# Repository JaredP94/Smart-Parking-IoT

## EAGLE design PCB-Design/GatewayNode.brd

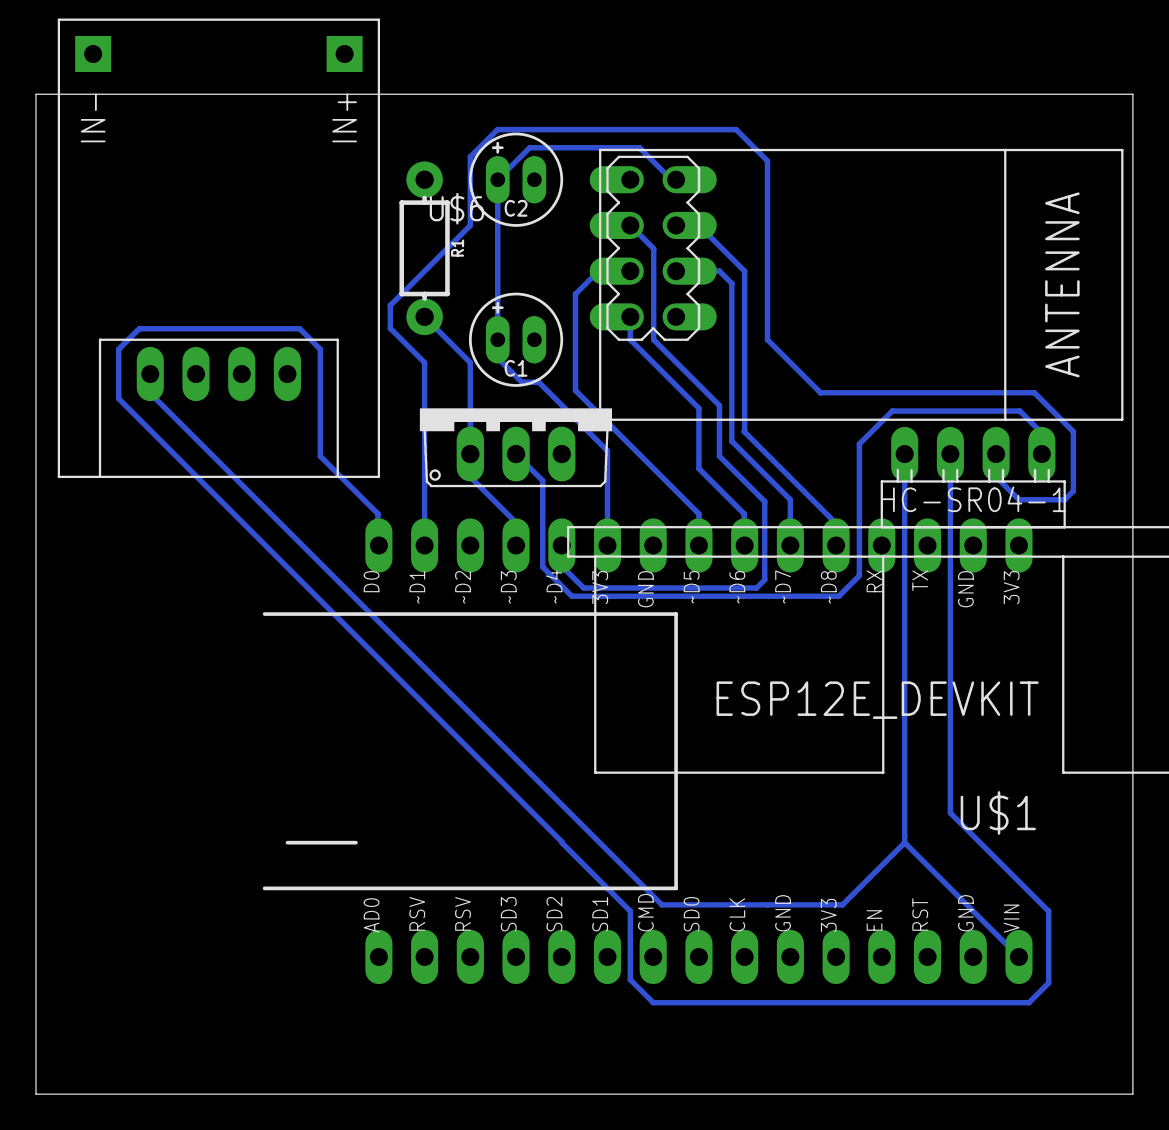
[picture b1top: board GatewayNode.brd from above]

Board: 2 copper layers, 60.9 x 55.5 mm, 8 parts (0 on the bottom side), 12 nets.

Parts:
C1, C2: 10U/35V; E2-5
HC-SR04-1: ULTRASONIC-HC-SR04#V
M3: WIRELESS-NRF24L01
R1: 10k; AXIAL-0.3-KIT
U$1: ESP12E_DEVKIT
U$5: DC-DC-STEP-UP-5V
U$6: IRL520N; TO220-VERT

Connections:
GND: C1.-, C2.-, M3.1, R1.P$1, U$1.GND@0, U$1.GND@1, U$1.GND@2, U$1.GND@3, U$5.GND, U$6.3
unnamed: R1.P$2, U$1.D3, U$6.1
unnamed: C1.+, C2.+, M3.2, U$1.3V3@1
unnamed: M3.3, U$1.D4
unnamed: M3.5, U$1.D5
unnamed: M3.7, U$1.D6
unnamed: M3.4, U$1.D8
unnamed: M3.6, U$1.D7
unnamed: HC-SR04-1.2, U$1.D0
unnamed: HC-SR04-1.4, U$6.2
unnamed: HC-SR04-1.3, U$1.D1
VCC: HC-SR04-1.1, U$1.VIN, U$5.5V

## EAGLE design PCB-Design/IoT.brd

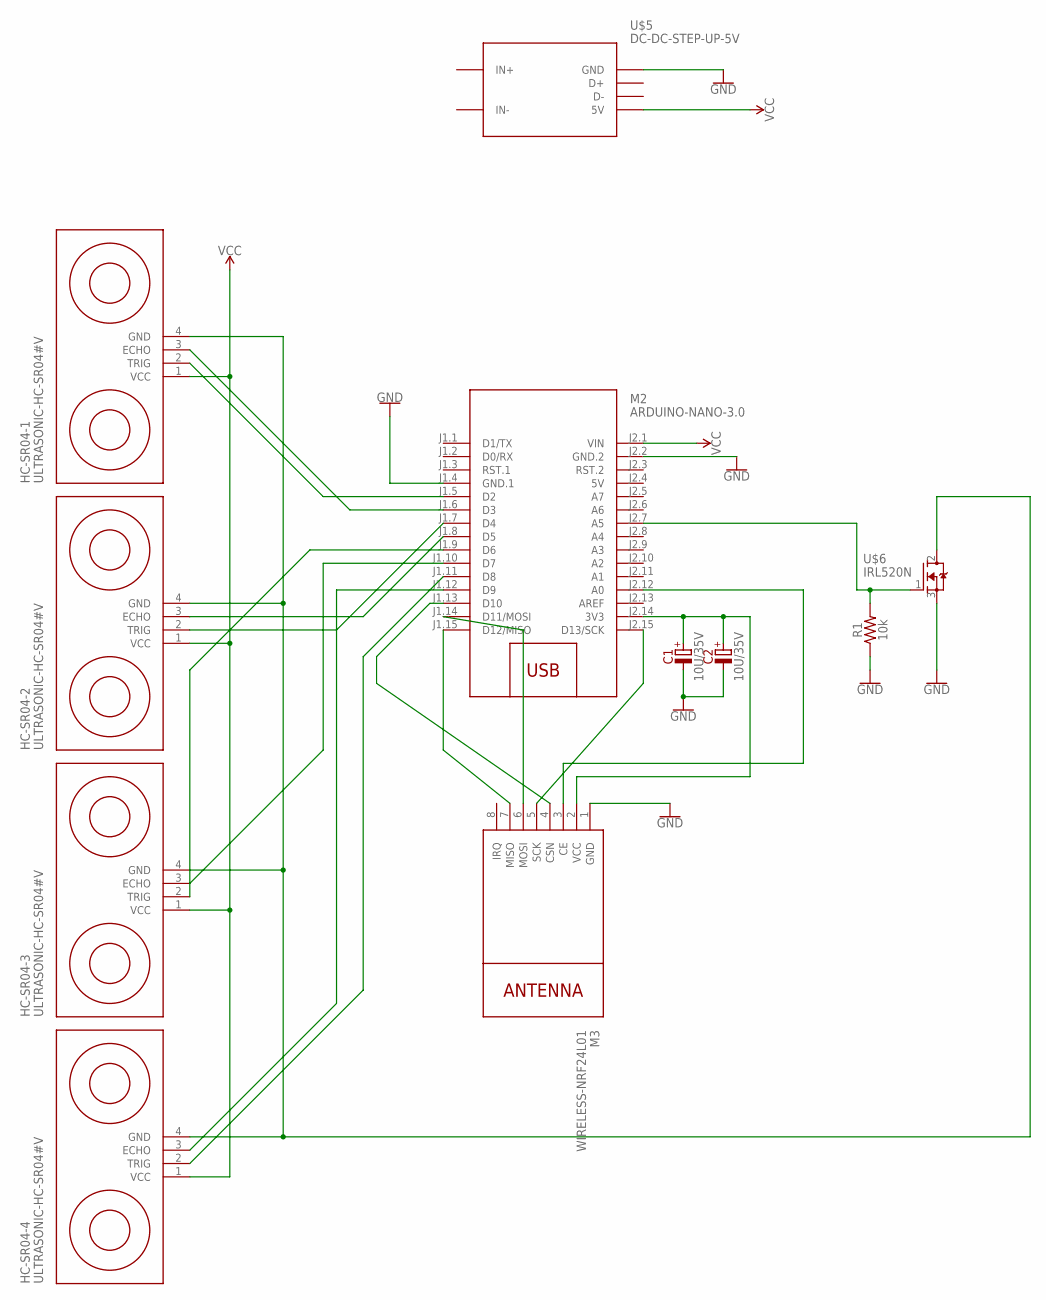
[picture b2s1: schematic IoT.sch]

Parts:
C1, C2: 10U/35V; E2-5
HC-SR04-1, HC-SR04-2, HC-SR04-3, HC-SR04-4: ULTRASONIC-HC-SR04#V
M2: ARDUINO-NANO-3.0
M3: WIRELESS-NRF24L01
R1: 10k; AXIAL-0.3-KIT
U$5: DC-DC-STEP-UP-5V
U$6: IRL520N; TO220-VERT

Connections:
5V: M2.J2.4 (5V)
GND: C1.-, C2.-, M2.J1.4 (GND.1), M2.J2.2 (GND.2), M3.1 (GND), R1.P$1 (1), U$5.GND, U$6.3 (S)
IN+: U$5.IN+
IN-: U$5.IN-
unnamed: M2.J2.7 (A5), R1.P$2 (2), U$6.1 (G)
unnamed: C1.+, C2.+, M2.J2.14 (3V3), M3.2 (VCC)
unnamed: HC-SR04-1.2 (TRIG), M2.J1.5 (D2)
unnamed: HC-SR04-1.3 (ECHO), M2.J1.6 (D3)
unnamed: HC-SR04-2.3 (ECHO), M2.J1.8 (D5)
unnamed: HC-SR04-2.2 (TRIG), M2.J1.7 (D4)
unnamed: HC-SR04-1.4 (GND), HC-SR04-2.4 (GND), HC-SR04-3.4 (GND), HC-SR04-4.4 (GND), U$6.2 (D)
unnamed: HC-SR04-3.3 (ECHO), M2.J1.10 (D7)
unnamed: HC-SR04-3.2 (TRIG), M2.J1.9 (D6)
unnamed: HC-SR04-4.3 (ECHO), M2.J1.12 (D9)
unnamed: HC-SR04-4.2 (TRIG), M2.J1.11 (D8)
unnamed: M2.J2.12 (A0), M3.3 (CE)
unnamed: M2.J1.13 (D10), M3.4 (CSN)
unnamed: M2.J2.15 (D13/SCK), M3.5 (SCK)
unnamed: M2.J1.14 (D11/MOSI), M3.6 (MOSI)
unnamed: M2.J1.15 (D12/MISO), M3.7 (MISO)
VCC: HC-SR04-1.1 (VCC), HC-SR04-2.1 (VCC), HC-SR04-3.1 (VCC), HC-SR04-4.1 (VCC), M2.J2.1 (VIN), U$5.5V

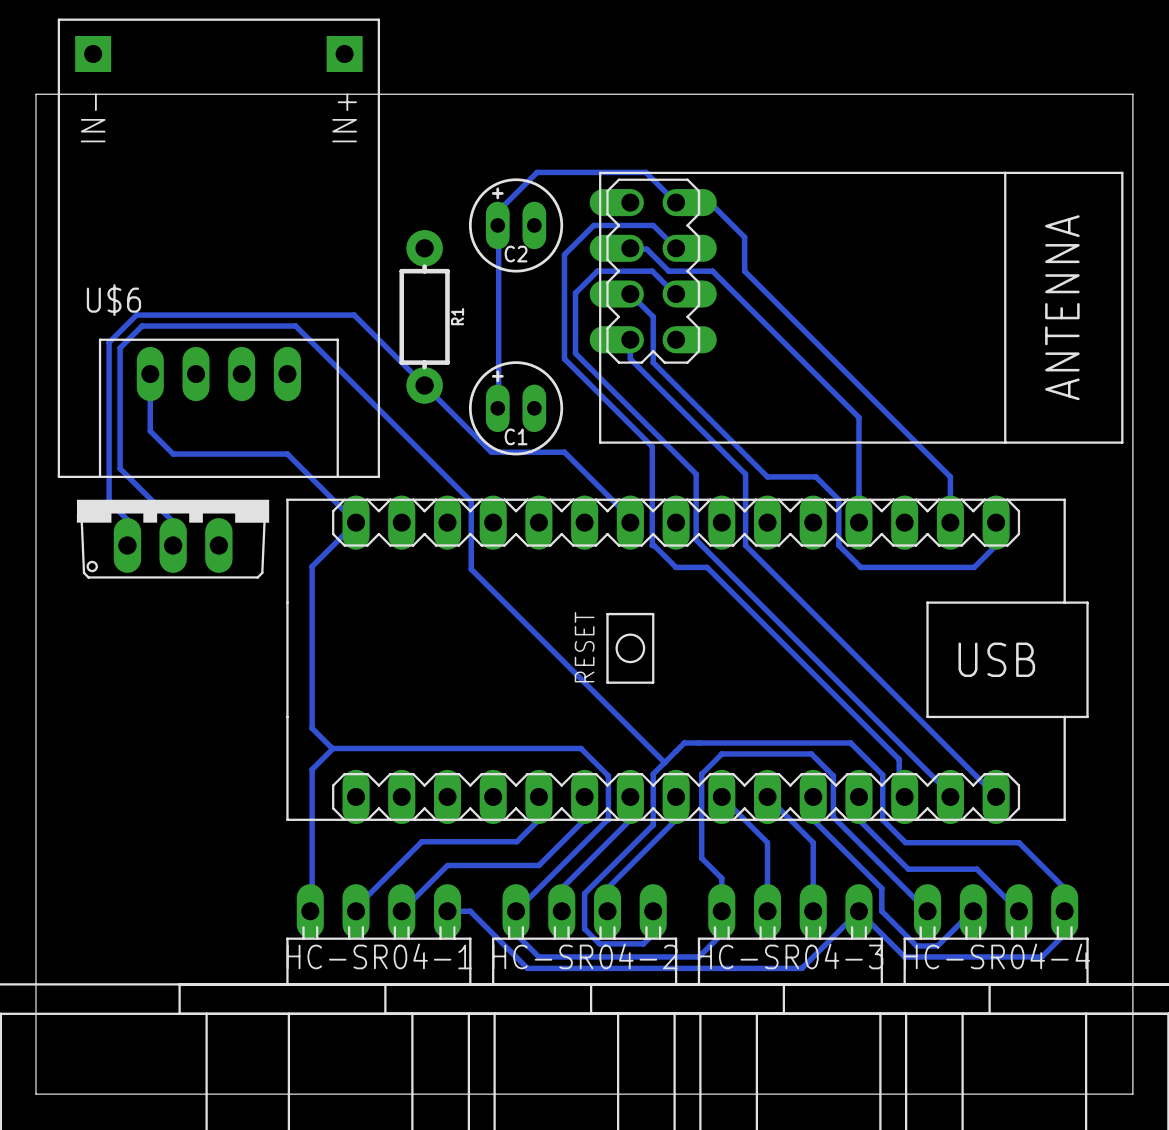
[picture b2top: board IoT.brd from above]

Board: 2 copper layers, 60.9 x 55.5 mm, 11 parts (0 on the bottom side), 18 nets.

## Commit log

2018-07-23 Gateway node
2018-07-23 Network detector
2018-07-23 RF transmit and receive templates
2018-07-23 sensorNode (collect distances) and prescaled transmitter (integer)
2018-07-23 Gateway node MAC address
2018-07-23 Use HashMap + Hide credentials
2018-07-23 HashMap library
2018-07-23 Prescaled reciever addition
2018-07-23 getDistance function added
2018-07-23 Added structs and checkOccupied function
2018-07-24 ESP Ping libraries + Ping test
2018-07-24 add SimpleMap
2018-07-24 Remove SimpleMap library
2018-07-24 Remove redundant SimpleMap code
2018-07-24 Cleanup, collect data as occupied and transmit as string
2018-07-24 deleted unnecessary
2018-07-24 Unabiz libraries
2018-07-24 Remove SimpleMap code
2018-07-24 SigFox upload
2018-07-25 strings send
2018-07-25 string receive - not working
2018-07-25 Transmit char wrrwy - working!
2018-07-26 Time SigFox transmission times
2018-07-27 WIP: PCB design
2018-07-27 WIP: PCB routing
2018-07-27 schematic - fixed mosfet and tidy up, board - manually routed (auto route super scary results)
2018-07-27 updated names on board
2018-07-27 more edits
2018-07-27 edits
2018-07-30 PCB edit
2018-07-30 Add some order
2018-07-30 Redone PCB on bottom only
2018-07-30 unsure about these changes
2018-07-30 Base application + Splash screen
2018-07-30 New PCB no wires necessary
2018-07-30 fixing git issues
2018-07-30 oops I did it again...
2018-07-30 more branding
2018-07-30 App rebrand
2018-07-31 Parking lot list activity + UI
2018-08-01 Parking lot grid with custom cell sizing + colour changeable cells
2018-08-01 Sensor node schematic and board rename
2018-08-01 WIP: Gateway node schematic and board
2018-08-03 Render road within parking lot
2018-08-08 ESP library for EAGLE
2018-08-09 Modify transmission data rate + Allow transmitter to use single sensor for demo
2018-08-09 LowPower library
2018-08-09 Implement 32 second sleep cycles with pause for radio input
2018-08-10 Create mesh network for bidirectional radio comms
2018-08-11 RF24Network library
2018-08-13 WIP: Gateway + Row Admin nodes
2018-08-13 Update gradle version + Cater for shitty res phone
2018-08-14 Node synchronisation + Power down after completed transmissions + Node hierarchy comms
2018-08-14 Sensor node in row
2018-08-15 Sensor Nodes 2 + 3
2018-08-15 Sensor nodes send data chunks + Row admin aggregates chunks for gateway
2018-08-15 Update parking bay colours
2018-08-15 Fix gridview scaling for HD devices
2018-08-16 Sensor node data sourced from sensors
2018-08-16 RowAdmin collects own sensor data while handling comms
2018-08-16 RowAdmin manages all sensor nodes in row
2018-08-16 Fix RowAdmin pin mappings
2018-08-16 Add RowAdmin headers for pinging Sensor Nodes
2018-08-16 Tried and tested Node 5
2018-08-16 Node 5 identifier
2018-08-16 Another header typo strikes
2018-08-16 Tried and tested Node 6
2018-08-16 Make addresses English
2018-08-16 Gateway to cater for multiple RowAdmin Nodes
2018-08-17 Node 5 Serial flush
2018-08-17 Node 6 Serial flush
2018-08-17 Update RowAdmin to cater for updated gateway
2018-08-17 Gateway ported to Arduino Nano for platform support
2018-08-17 Remove need for independent gateway node
2018-08-17 RowAdmin per row
2018-08-17 Remove redundant comment
2018-08-17 Updated Gateway Node with Sensor Node capabilities
2018-08-18 Delay RowAdmin retransmission attempts
2018-08-18 Send Gateway Node data to Transmitter Node
2018-08-18 Transmitter Node receives and stores data for upload
2018-08-20 Change Unsigned Char to Char
2018-08-20 Accomodate updated char arrays
2018-08-20 Transmitter node
2018-08-21 Functional HTTP GET requests + JSON response parsing + Available Parkings Stats + Further enchancing custom RecyclerView + WIP: UI styling and animation
2018-08-22 Update sensor pins + Data rate for sensorNode template
2018-08-22 Updated transmission data type + Sensor pin config for Mesh Sensor Nodes
2018-08-22 Ignore credentials files
2018-08-22 Update JDK version
2018-08-22 Transmitter with updated MQTT broker + Reconnection ability
2018-08-22 Obtain parking data + propagate data through activities + render parkings
2018-08-22 UI/UX changes for parking rendering and interaction
2018-08-23 Update timeout distance
2018-08-23 Fix pin mappings + Max sensor distance
2018-08-23 Auto update data query for parking lot
2018-08-24 Loading screen before parking lot is loaded
2018-08-24 Resolution scalability
2018-08-24 Update pin mappings + Correct sleep times
2018-08-24 Reconfigure Node 1 + Transmission ACK
2018-08-24 Reconfigure Node2
2018-08-24 Reconfigure Node3
2018-08-24 Fix name
2018-08-24 Reconfigure Node5
2018-08-24 Reconfigure Node6
2018-08-24 Configure Node7
2018-08-24 Enable reconnection if MQTT broker connection fails
2018-08-24 Rebuild + UI tweaks + Sync time reduced
2018-08-24 final gateway node PCB design
2018-08-24 IEEE poster template
2018-08-24 tiny bit of poster, some general stuff
2018-08-24 Configure Open Day Node
2018-08-24 Updated Parking Lot Class Structure
2018-08-24 Add processing of multiple lot results from different channels + Adjust app flow to cater for multiple lots
2018-08-24 Move info to Credentials file
2018-08-25 Reconfigure Open Day Node
2018-08-25 Change orientation for Open Day activity + Parking lot styling
2018-08-25 intro, objectives and future - POSTER
2018-08-25 Time node operations + Boost radio power level + Imrpove synchronisation
2018-08-25 Adjust power levels + sleep time for Transmitter + Gateway
2018-08-25 Reconfigure Node 2
2018-08-26 Reconfigure Node 1
2018-08-26 Reconfigure Node 3
2018-08-26 Reconfigure Node 4
2018-08-26 Reconfigure Node 5
2018-08-26 Reconfigure Node 6
2018-08-26 Node 7
2018-08-26 Configure Node 8
2018-08-26 Reconfigure Node 9
2018-08-26 Configure Node 11
2018-08-26 Configure Node 12
2018-08-26 Configure Node 13
2018-08-26 Configure Node 14
2018-08-26 Configure Node 15
2018-08-26 Reconfigure Node 16
2018-08-26 Configure Node 17
2018-08-26 Configure Node 18
2018-08-26 Remove non-existant parking lot bays
2018-08-26 Improved splash screen
2018-08-26 poster stuff and stuff
2018-08-26 Poster, almost there, sleep time
2018-08-26 Updated screenshot to have legend
2018-08-26 Larger legend size
2018-08-26 Fix JsonObjectRequest ordering on app load
2018-08-26 Improve colour contrasts
2018-08-26 updated font scale slightly
2018-08-26 Update logo
2018-08-26 Update loading screen transition
2018-08-26 Update splash screen
2018-08-26 App restart on network failure
2018-08-26 Edits + Additions
2018-08-26 Poster edits
2018-08-26 Merge
2018-08-26 Adjust loading screen text
2018-08-26 Poster possibly final version
2018-08-26 Prepare for release
2018-08-26 one last spacing change
2018-08-26 Poster
2018-08-26 Updated poster pdf
2018-08-26 line spacing
2018-08-26 Final updates
2018-08-27 Reduced distance for demo node
2018-08-27 Updated app to cater for improved SDK support range
2018-09-02 Add thingspeak logs for last 100 uploads
2018-09-02 Remove csv formatting
2019-10-10 Create LICENSE

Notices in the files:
parts and their libraries:
diy-modules: Released under the Creative Commons Attribution 4.0 International License: http://creativecommons.org/licenses/by/4.0
SparkFun-Resistors: Licensing: Creative Commons ShareAlike 4.0 International - https://creativecommons.org/licenses/by-sa/4.0
